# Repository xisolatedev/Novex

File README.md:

# Novex

Novex is an experimental embodied AI platform that connects AI, drones, spatial computing, VR, and wireless communication. NOVA allows a user to communicate with and command robotic agents through natural interaction while onboard systems handle perception, navigation, collision avoidance, and real-time control.

# Novex

### Embodied AI • Spatial Computing • Autonomous Robotics

**Novex** is an experimental embodied AI platform designed to connect artificial intelligence with the physical world through autonomous robotic systems.

Novex combines **AI reasoning, real-time control, computer vision, SLAM, spatial computing, wireless communication, and robotic agents** into a single ecosystem.

The goal is

> **Giving AI the ability to perceive, understand, and interact with the physical world.**

---

## Architecture

Novex is designed as a layered system rather than one large AI model.

---

## Robotic Agents

Novex uses robotic agents as the physical embodiment of the system.

A drone can contain:

* Stereo or multiple cameras
* IMU
* Onboard computing
* Wireless communication
* Battery monitoring
* Spatial perception
* Local safety systems
* Real-time control software

The drone itself does not need to understand natural language. It receives structured missions and continuously executes them through its onboard control system.

---

## GO — Fast Control Policy

GO is Novex's lightweight real-time control layer.

Instead of using a large language model for every control decision, GO continuously processes the drone's current state and mission objective.

GO is intended to operate at a much higher frequency than the high-level reasoning system.

This separates **reasoning** from **reflexive control**.

---

## Controller Interface

Novex can interface with existing robotic platforms through hardware-specific controller adapters.

The fast policy produces normalized control values, which are then translated by an adapter into the appropriate control representation for the target platform.

```text
GO
 ↓
Normalized Control State
 ↓
Controller Adapter
 ↓
Protocol / Signal Encoding
 ↓
Robot
```

This abstraction allows the same control architecture to potentially support different robotic platforms without rebuilding the AI system.

---

## Spatial Perception

Novex uses computer vision and sensor fusion to estimate the physical environment.

Stereo cameras can provide depth information while visual odometry and inertial measurements help estimate movement.

```text
Stereo Camera ──┐
                ├──→ Sensor Fusion
IMU ────────────┘
                      │
                      ▼
              Position / Velocity
                      │
                      ▼
                  World Model
```

The system can use this information for navigation, spatial interaction, and collision awareness.

---

## Safety & Collision Detection

Safety is intentionally separated from high-level AI.

The AI may request an action, but an independent safety layer can reject or modify unsafe commands.

```text
             AI
              │
              ▼
        Desired Motion
              │
              ▼
       ┌──────────────┐
       │    SAFETY    │
       │    SYSTEM    │
       └──────┬───────┘
              │
        Safe / Blocked
              │
              ▼
           Control
```

This prevents a faulty model or incorrect command from directly determining physical behavior.

---

## NoRA

**NoRA** is the infrastructure and communication layer surrounding Novex.

Rather than being solely a drone-control protocol, NoRA is designed to connect:

* Homes
* Charging stations
* Relay nodes
* Robotic agents
* Local services
* User devices

The phone acts as the primary human controller, while NoRA provides communication between the wider ecosystem.

---

## Autonomous Infrastructure

Novex can incorporate charging and docking stations into the robotic ecosystem.

A drone can:

1. Complete a mission
2. Monitor battery state
3. Determine whether it should return
4. Navigate toward a known station
5. Dock
6. Recharge
7. Remain available for future missions

This allows robotic agents to operate as part of an ecosystem rather than as isolated devices.

---

## High-Level AI

Novex's high-level AI can be connected to an LLM for natural interaction and mission planning.

> **We are also thinking of putting a slm or collective on device ai
> **Experimenting with radio weights
> For example:

```text
"Keep Drone 1 near me and have
Drones 2 and 3 orbit around it."
-This isnt a real example but thoughts.
```

The LLM can translate the request into a structured mission.

The mission is then passed to the real-time control system.

The LLM **plans**.

GO **executes**.

The safety system **guards**.

---

## Long-Term Vision

Novex is ultimately exploring a larger question:

> **What happens when AI is no longer limited to a screen?**

Instead of an AI existing only inside a computer, Novex explores an AI that can:

**See → Understand → Plan → Act → Observe → Adapt**

through a network of physical robotic agents.

The long-term vision is a distributed embodied intelligence platform where **humans, AI, robots, spatial environments, and infrastructure operate together as one system.**

---

## Project Status

Novex is an experimental research and development project.

Current areas of development include:

* [ ] Drone hardware platform
* [ ] Controller interface
* [ ] Onboard computing
* [ ] Stereo vision
* [ ] State estimation
* [ ] Collision detection
* [ ] GO policy
* [ ] Nova AI integration
* [ ] NoRA communication layer
* [ ] Charging/docking system
* [ ] VR spatial interface
* [ ] Multi-agent coordination
* [ ] Swarm experimentation

---

## Safety

Novex involves physical robotic systems.

Early development should go for simulation, bench testing, controlled environments, low-energy experiments, and independent safety systems before attempting autonomous flight.

The objective is to make the system **predictable before making it autonomous.**

Love this since we need to understand the actions before making it autonomous.

3D generated Simulation is still in the works.

---

## Philosophy

Novex is built around one principle:

> **Don't make one giant AI do everything. Build systems that specialize.**

1. A fast controller handles reflexes.
2. A spatial system handles perception.
3. An AI handles reasoning.
4. A communication layer connects everything.
5. A safety system keeps the physical world from becoming a debugging loop.

And the commander remains in control.

Im looking forward to documented flights, 3D map representation, Scans, Personal Clouds, and SATCOM (Sattelite like imagery and data connection)

## Schematics

Firmware isnt fully tested to hardware
V2 Prototype underway.
-Ommidirectional Mircophone Array
-4G Connection
-Mesh Network Worker / Tower Brodcaster

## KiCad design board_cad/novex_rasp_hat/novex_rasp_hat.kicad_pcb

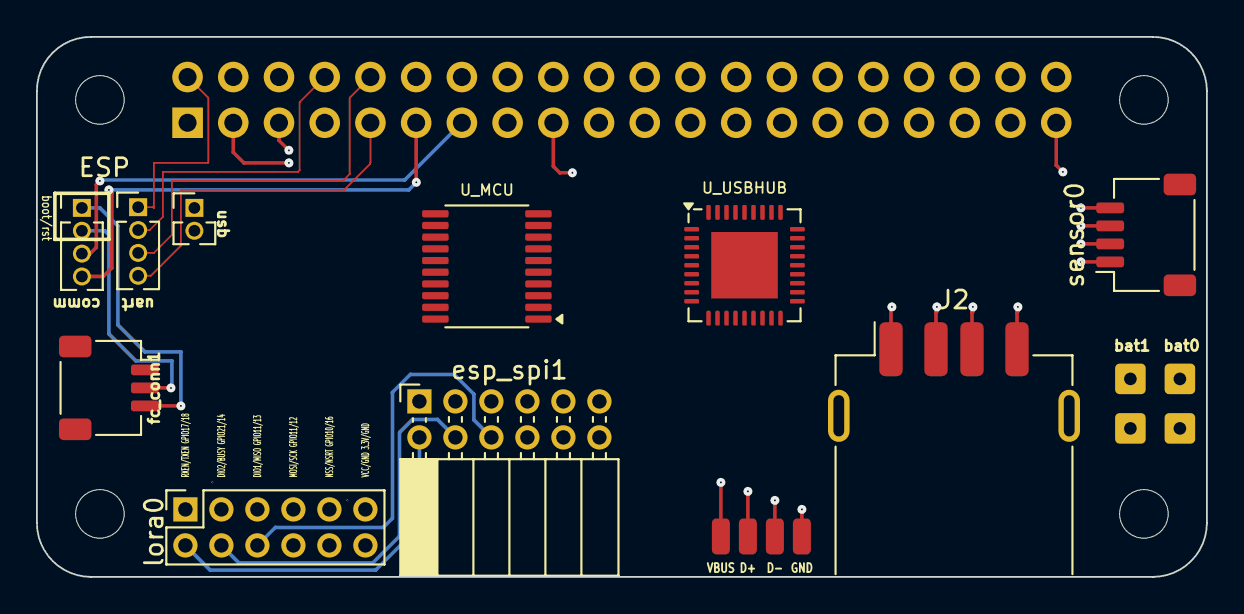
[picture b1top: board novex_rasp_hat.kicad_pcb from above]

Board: 4 copper layers, 65.0 x 30.0 mm, 23 parts (1 on the bottom side), 23 nets.

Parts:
D+: TestPoint; SolderWirePad_1x01_SMD_1x2mm
D-: TestPoint; SolderWirePad_1x01_SMD_1x2mm
ESP_USB: PinHeader_1x02_P1.27mm_Vertical
GND: TestPoint; SolderWirePad_1x01_SMD_1x2mm
J1: GPIO; PinSocket_2x20_P2.54mm_Vertical
J2: USB_A; USB_A_Receptacle_GCT_USB1046
MH1, MH2, MH3, MH4: MountingHole_2.7mm_M2.5
U_MCU: TSSOP-20_4.4x6.5mm_P0.65mm
U_USBHUB: QFN-36-1EP_6x6mm_P0.5mm_EP3.7x3.7mm
VBUS: TestPoint; SolderWirePad_1x01_SMD_1x2mm
bat0+, bat0-, bat1+, bat1-: SolderWire-0.127sqmm_1x01_D0.48mm_OD1mm
esp_comm1: Conn_01x04; PinHeader_1x04_P1.27mm_Vertical
esp_spi1: Conn_02x06_Odd_Even; PinSocket_2x06_P2.00mm_Horizontal
esp_uart_0: Conn_01x04; PinHeader_1x04_P1.27mm_Vertical
fc_conn1: Conn_01x03; JST_SH_SM03B-SRSS-TB_1x03-1MP_P1.00mm_Horizontal
lora0: Conn_02x06_Odd_Even; PinSocket_2x06_P2.00mm_Vertical
sensor0: Conn_01x04; JST_SH_SM04B-SRSS-TB_1x04-1MP_P1.00mm_Horizontal

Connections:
+3V3: J1.1, J1.17, sensor0.2
+5V: J1.2, J1.4, esp_uart_0.1
/GPIO14/TXD0: J1.8, esp_uart_0.2
/GPIO15/RXD0: J1.10, esp_uart_0.3
GND: J1.6, J1.9, J1.14, J1.20, J1.25, J1.30, J1.34, J1.39, esp_uart_0.4, sensor0.1
unnamed: esp_comm1.1, fc_conn1.3
unnamed: esp_comm1.2, fc_conn1.2
unnamed: esp_spi1.1, lora0.1
unnamed: esp_spi1.2, lora0.2
unnamed: esp_spi1.3, lora0.3
unnamed: esp_spi1.4, lora0.4
unnamed: esp_spi1.5, lora0.5
unnamed: esp_spi1.6, lora0.6
unnamed: esp_spi1.7, lora0.7
unnamed: esp_spi1.8, lora0.8
unnamed: esp_spi1.9, lora0.9
unnamed: esp_spi1.10, lora0.10
unnamed: esp_spi1.11, lora0.11
unnamed: esp_spi1.12, lora0.12
SCL: J1.5, sensor0.4
SDA: J1.3, sensor0.3
esp_boot: J1.13, esp_comm1.3
esp_rst: J1.11, esp_comm1.4
